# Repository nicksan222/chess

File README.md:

<div align="center">

# Chess

### A physical chessboard with software in its bones.

**64 magnetic sensors · 64 RGB lights · one Raspberry Pi · zero hidden magic**

[**Explore the hardware**](hardware/README.md) · [**Read the architecture**](docs/architecture.md) · [**Build from source**](docs/development.md) · [**Contribute**](.github/CONTRIBUTING.md)

<sub>Not a product mockup—the render above is generated from the <a href="hardware/cad/generated/board-assembly.blend">Blender assembly model in this repository</a>.</sub>

</div>

## About

Chess is an open-source smart chessboard designed to make the physical game
programmable. The design gives every square its own magnetic piece sensor and
clocked RGB light, ready to illuminate moves, threats, prompts, or entirely new
game modes. A Raspberry Pi Zero 2 W is intended to run the board directly in
Rust—there is no microcontroller, companion firmware, or private protocol in
the middle.

The interesting part is not only the board. Its mechanical dimensions,
electrical connectivity, firmware pin maps, KiCad project, Blender models, BOM,
and review images are generated from version-controlled contracts. Change a
measurement or signal once, regenerate, and let tests catch disagreement across
the stack.

| | |
|---|---|
| **Sense** | 64 DRV5032FC Hall sensors, eight compact polled TCA9554 banks |
| **Glow** | 64 individually addressable SK9822 RGB LEDs |
| **Think** | Raspberry Pi Zero 2 W targeting Rust on a Yocto Linux image |
| **Interact** | 12 labelled physical buttons and a 2.42-inch monochrome I²C OLED |
| **Build** | One 320 × 380 mm PCB, case, plate and twelve printable button caps |
| **Design** | Python contracts → KiCad 9 + Blender 4.5 + firmware mappings |

## Peek under the board

<table>
  <tr>
    <td width="58%">
      
    </td>
    <td width="42%">
      
    </td>
  </tr>
  <tr>
    <td align="center"><strong>Two printed parts. One PCB. No per-square wiring harness.</strong></td>
    <td align="center"><strong>Every square gets a sensor and an LED.</strong></td>
  </tr>
</table>

The visuals are review artifacts, not hand-drawn diagrams. Open the
[Blender assembly](hardware/cad/generated/board-assembly.blend), inspect the
[KiCad board](hardware/pcb/generated/chess-board.kicad_pcb), browse the
[generated schematic](hardware/pcb/generated/schematic/chess-board.svg), or
check every exact part in the [generated BOM](hardware/pcb/generated/bom.csv).

## Why this is fun to hack on

| Hardware you can reason about | Software with clean seams | A workflow built for changes |
|---|---|---|
| No second processor and no opaque wire protocol. The Pi talks to I²C expanders, SPI LEDs, GPIO buttons, and the display directly. | The chess engine, menu model, persistence, and Pi application live in separate Rust crates. | One devcontainer pins Rust, Ruff, KiCad, Blender, and Just. CI checks code, connectivity, layout, CAD, and the AArch64 firmware graph. |

```mermaid
flowchart LR
    P["Magnetic pieces"] --> H["64 × Hall sensors"]
    H --> E["8 × TCA9554 banks (2×4)"]
    E --> PI["Raspberry Pi Zero 2 W"]
    PI --> R["Rust chess + board logic"]
    PI --> L["64 × RGB LEDs"]
    PI --> UI["OLED + 12 buttons"]
```

Read the [architecture notes](docs/architecture.md) for the boundaries and the
[hardware design](docs/hardware.md) for the component choices behind them.

## Repository tour

| Path | What is inside |
|---|---|
| [`apps/firmware`](apps/firmware) | The Raspberry Pi process, system integration, and Yocto image |
| [`crates`](crates/README.md) | Chess rules, menu state, persistence, logging, and shared Rust code |
| [`hardware/shared`](hardware/shared) | The source of truth for dimensions, parts, wiring, and mappings |
| [`hardware/pcb`](hardware/pcb) | PCB definition, routing, validation, KiCad project, and BOM |
| [`hardware/cad`](hardware/cad) | Parametric enclosure generators, Blender models, and renders |
| [`docs`](docs/README.md) | Architecture, fabrication, power, assembly, and development guides |

## Start hacking

Clone the repository, open it in the included
[development container](.devcontainer/README.md), and then use its pinned
toolchain:

```bash
just --list       # discover everything the repo can do
just precommit    # fast code + hardware validation
just generate     # regenerate CAD and PCB review artifacts
just check        # run routine repository-wide validation
```

Physical-release and Linux-image validation remain explicit, separate gates:

```bash
just pcb-release
just firmware-check
```

Prefer a smaller loop? Every app, crate, and hardware domain owns its own
`justfile`:

```bash
just --justfile crates/chess/justfile check
just --justfile hardware/pcb/justfile review
just --justfile hardware/cad/justfile generate
```

See [`docs/development.md`](docs/development.md) for the full workflow.

Coding assistants start from [`AGENTS.md`](AGENTS.md). Claude Code, Codex and
other harnesses share one set of [skills and subagent roles](.agents/README.md),
including firmware, hardware, mechanical and manufacturing engineers; the
session you start delegates to them as needed.

## Project status

> [!IMPORTANT]
> **The current design is ready for review, not yet physically proven.** The
> mechanical design and `D-PROTOTYPE` PCB generate successfully, and automated
> DRC, connectivity, schematic parity and modeled electrical checks pass;
> meaningful ERC still requires declared electrical pin roles. No
> complete board has been built yet. Prototype one sensor/LED square before
> ordering the full PCB.

The chess model and supervised firmware process exist, and the firmware polls
buttons and Hall-sensor banks. The LED worker, provisioning workers, and final
physical validation are still open territory.
That makes this a particularly good time to challenge assumptions and shape the
project rather than only polish a finished product.

## Pick a quest

- **Firmware:** connect the Rust application to real Linux character devices.
- **Simulator:** make board behavior fast to test without a soldering iron.
- **Electronics:** review sensing, power, routing, and manufacturability.
- **Mechanical:** test clearances, print strategy, materials, and light diffusion.
- **Docs:** turn a pile of generated artifacts into a delightful build journey.

Start with [`CONTRIBUTING.md`](.github/CONTRIBUTING.md), bring large ideas to
[Discussions](https://github.com/nicksan222/chess/discussions), and use the issue
forms for focused bugs or features. First-time contributors are very welcome.

---

<div align="center">

**Build it. Break it. Teach it a new game.**

Released under the [MIT License](LICENSE) · Please follow the
[Code of Conduct](.github/CODE_OF_CONDUCT.md) · Report security issues via
[`SECURITY.md`](.github/SECURITY.md)

</div>

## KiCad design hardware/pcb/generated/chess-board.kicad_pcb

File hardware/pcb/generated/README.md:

# Generated PCB

Source: `pcb.board.board.Board()`. Regenerate with `PYTHONPATH=hardware python3 -m pcb.board.generate`.

Open `chess-board.kicad_pro` in KiCad. Schematics embed all symbols and show the declared pin maps; PCB footprints come from component land patterns. The exported schematic netlist is checked against every declared connected pin.

The PCB includes routed copper, filled internal rail planes, mounting holes and assembly markings. `chess-board.glb` is the native 3D assembly imported by CAD; `models/` contains portable STEP bodies and `3d-models.json` records fidelity and provenance. ERC/DRC findings are in `erc.json` and `drc.json`. Electrical pin roles are unspecified; ERC does not validate driver/power compatibility. `board-top.svg` and `board-top.png` show the same copper view; bottom views are mirrored. `board-connections.svg` shows logical connectivity as dashed airwires, not extra copper. `manifest.json` lists remaining work. The fabrication ZIP contains Gerbers and drill files; generating it does not approve manufacturing.

Board-specific sensing and button simulations passed; results are in `electrical-checks/`. These use ideal sensor, contact and external GPIO bias models; I2C, magnetic margins, firmware debounce and a complete board model remain untested.

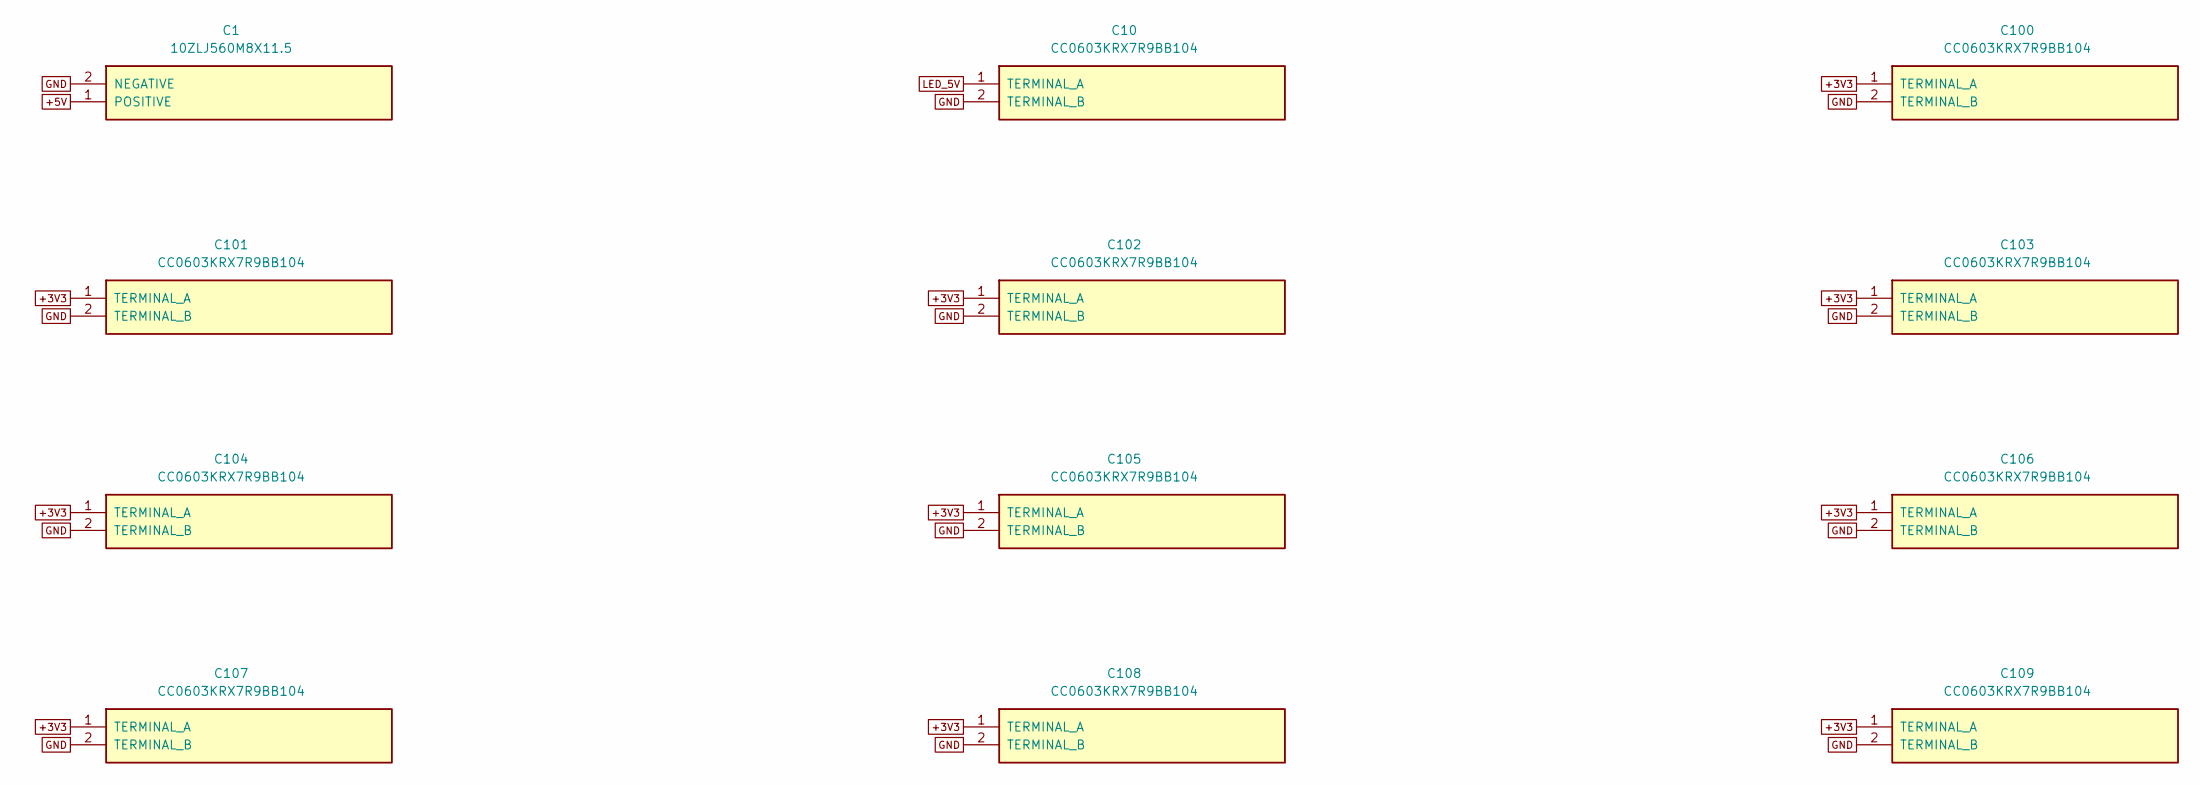
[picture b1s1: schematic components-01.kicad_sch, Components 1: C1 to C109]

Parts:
C1: 10ZLJ560M8X11.5; CAP_560U
C10, C100, C101, C102, C103, C104, C105, C106, C107, C108, C109: CC0603KRX7R9BB104; CAP_100N

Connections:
+3V3: C100.1 (TERMINAL_A), C101.1 (TERMINAL_A), C102.1 (TERMINAL_A), C103.1 (TERMINAL_A), C104.1 (TERMINAL_A), C105.1 (TERMINAL_A), C106.1 (TERMINAL_A), C107.1 (TERMINAL_A), C108.1 (TERMINAL_A), C109.1 (TERMINAL_A); also elsewhere on the board
+5V: C1.1 (POSITIVE); also elsewhere on the board
GND: C1.2 (NEGATIVE), C10.2 (TERMINAL_B), C100.2 (TERMINAL_B), C101.2 (TERMINAL_B), C102.2 (TERMINAL_B), C103.2 (TERMINAL_B), C104.2 (TERMINAL_B), C105.2 (TERMINAL_B), C106.2 (TERMINAL_B), C107.2 (TERMINAL_B), C108.2 (TERMINAL_B), C109.2 (TERMINAL_B); also elsewhere on the board
LED_5V: C10.1 (TERMINAL_A); also elsewhere on the board

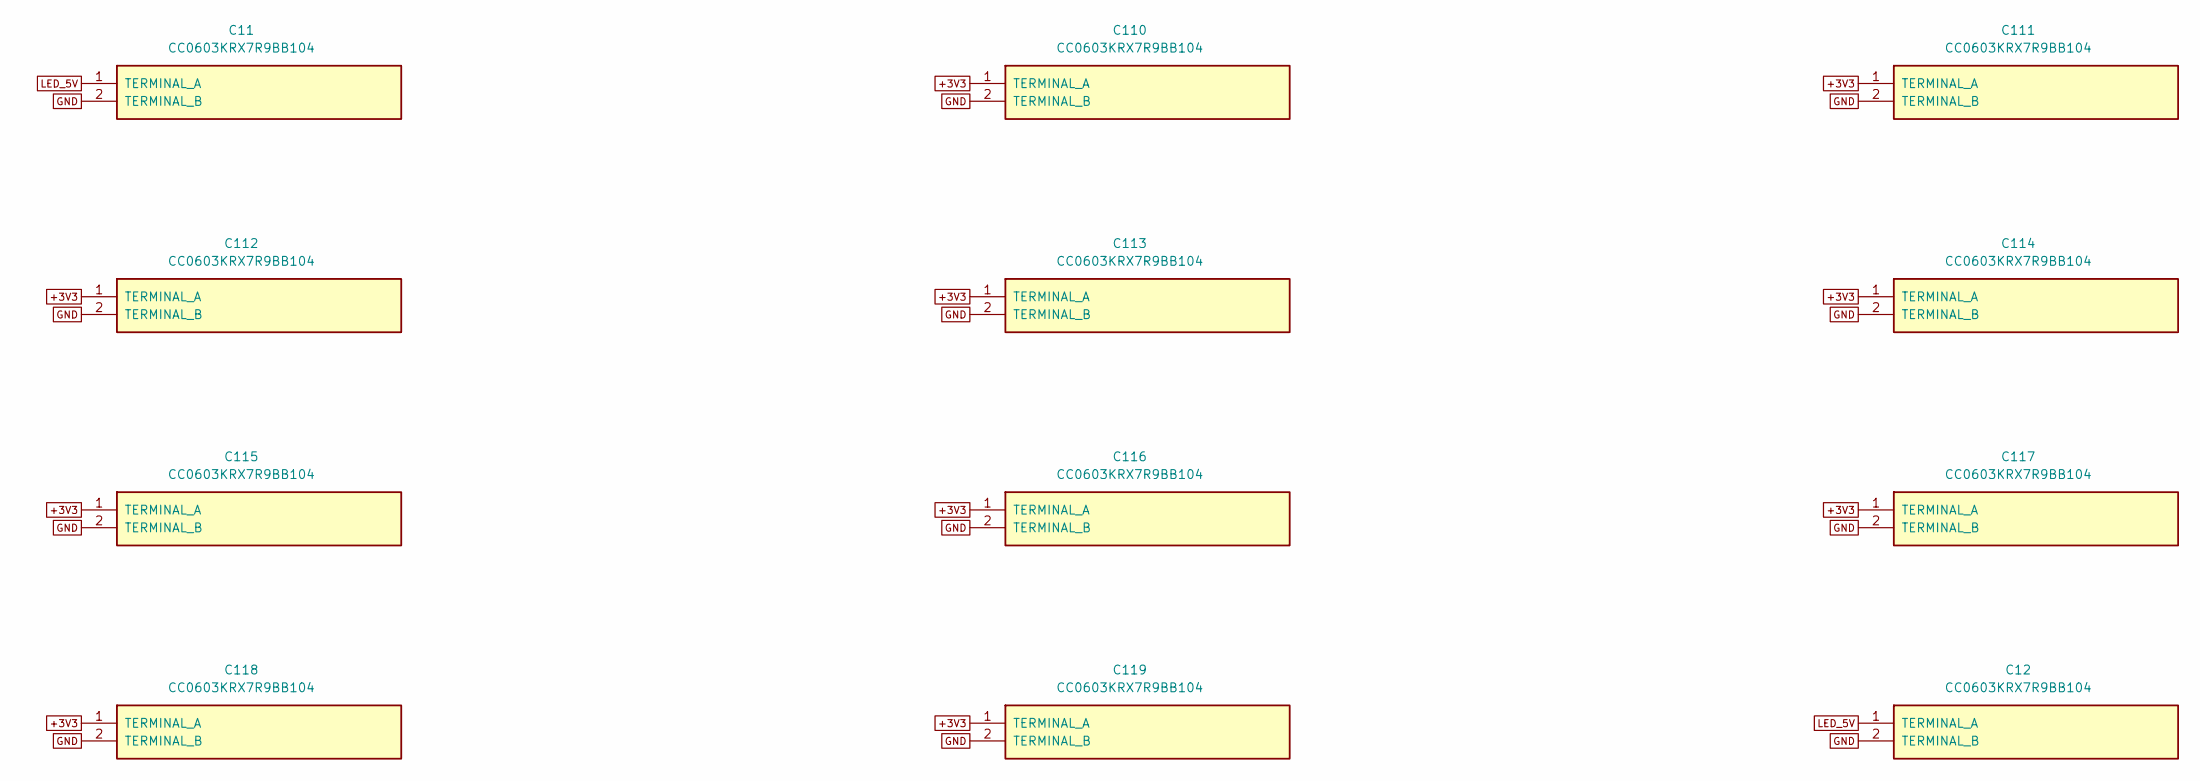
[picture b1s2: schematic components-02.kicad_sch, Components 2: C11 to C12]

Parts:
C11, C12, C110, C111, C112, C113, C114, C115, C116, C117, C118, C119: CC0603KRX7R9BB104; CAP_100N

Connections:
+3V3: C110.1 (TERMINAL_A), C111.1 (TERMINAL_A), C112.1 (TERMINAL_A), C113.1 (TERMINAL_A), C114.1 (TERMINAL_A), C115.1 (TERMINAL_A), C116.1 (TERMINAL_A), C117.1 (TERMINAL_A), C118.1 (TERMINAL_A), C119.1 (TERMINAL_A); also elsewhere on the board
GND: C11.2 (TERMINAL_B), C12.2 (TERMINAL_B), C110.2 (TERMINAL_B), C111.2 (TERMINAL_B), C112.2 (TERMINAL_B), C113.2 (TERMINAL_B), C114.2 (TERMINAL_B), C115.2 (TERMINAL_B), C116.2 (TERMINAL_B), C117.2 (TERMINAL_B), C118.2 (TERMINAL_B), C119.2 (TERMINAL_B); also elsewhere on the board
LED_5V: C11.1 (TERMINAL_A), C12.1 (TERMINAL_A); also elsewhere on the board

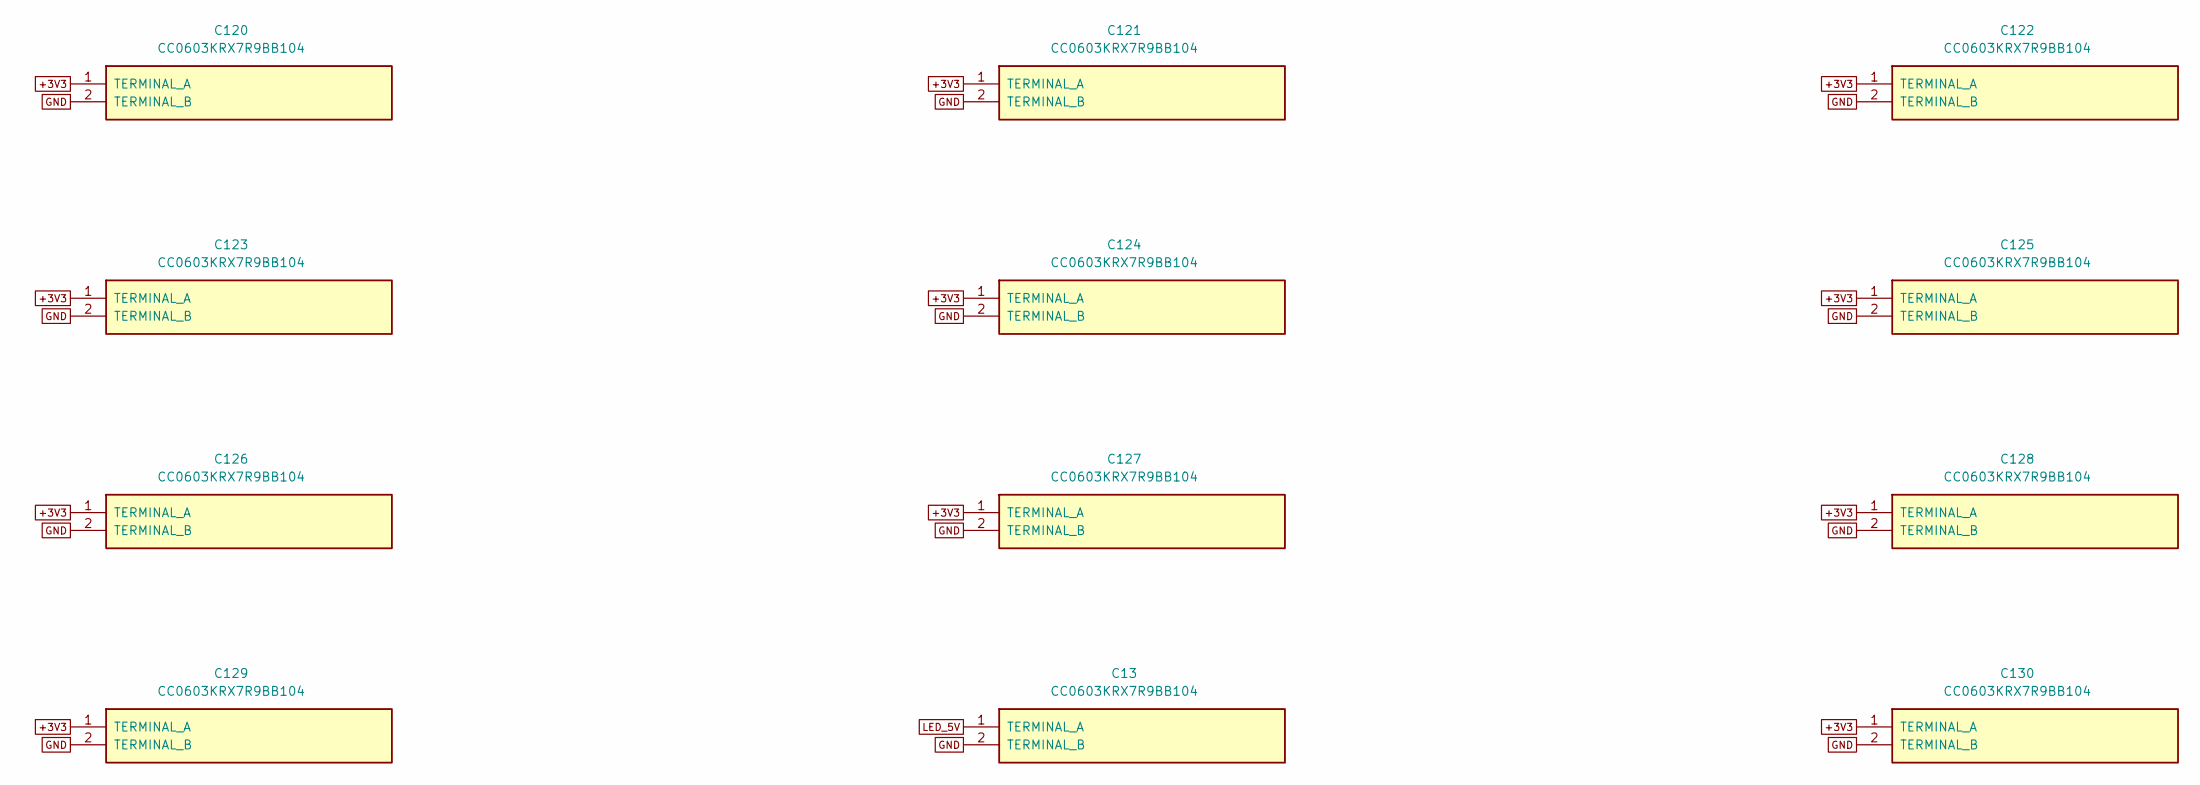
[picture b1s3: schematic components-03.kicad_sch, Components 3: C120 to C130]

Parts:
C13, C120, C121, C122, C123, C124, C125, C126, C127, C128, C129, C130: CC0603KRX7R9BB104; CAP_100N

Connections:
+3V3: C120.1 (TERMINAL_A), C121.1 (TERMINAL_A), C122.1 (TERMINAL_A), C123.1 (TERMINAL_A), C124.1 (TERMINAL_A), C125.1 (TERMINAL_A), C126.1 (TERMINAL_A), C127.1 (TERMINAL_A), C128.1 (TERMINAL_A), C129.1 (TERMINAL_A), C130.1 (TERMINAL_A); also elsewhere on the board
GND: C13.2 (TERMINAL_B), C120.2 (TERMINAL_B), C121.2 (TERMINAL_B), C122.2 (TERMINAL_B), C123.2 (TERMINAL_B), C124.2 (TERMINAL_B), C125.2 (TERMINAL_B), C126.2 (TERMINAL_B), C127.2 (TERMINAL_B), C128.2 (TERMINAL_B), C129.2 (TERMINAL_B), C130.2 (TERMINAL_B); also elsewhere on the board
LED_5V: C13.1 (TERMINAL_A); also elsewhere on the board

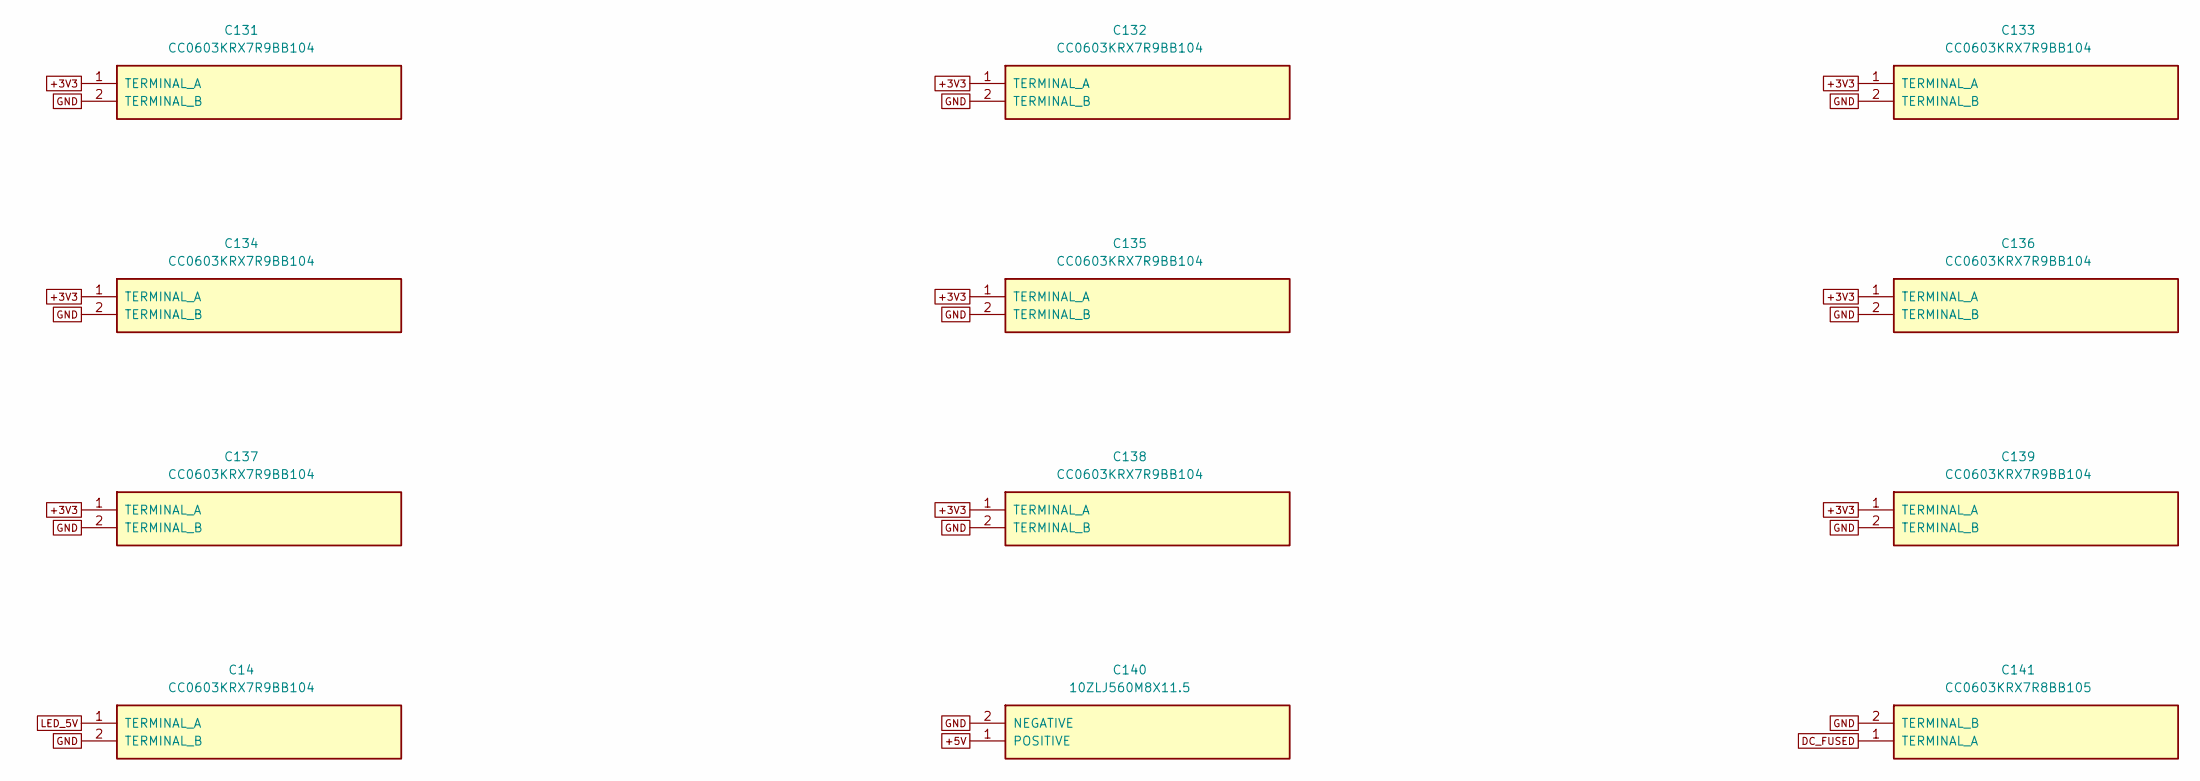
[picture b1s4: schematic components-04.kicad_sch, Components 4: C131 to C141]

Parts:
C14, C131, C132, C133, C134, C135, C136, C137, C138, C139: CC0603KRX7R9BB104; CAP_100N
C140: 10ZLJ560M8X11.5; CAP_560U
C141: CC0603KRX7R8BB105; CAP_1U

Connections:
+3V3: C131.1 (TERMINAL_A), C132.1 (TERMINAL_A), C133.1 (TERMINAL_A), C134.1 (TERMINAL_A), C135.1 (TERMINAL_A), C136.1 (TERMINAL_A), C137.1 (TERMINAL_A), C138.1 (TERMINAL_A), C139.1 (TERMINAL_A); also elsewhere on the board
+5V: C140.1 (POSITIVE); also elsewhere on the board
DC_FUSED: C141.1 (TERMINAL_A); also elsewhere on the board
GND: C14.2 (TERMINAL_B), C131.2 (TERMINAL_B), C132.2 (TERMINAL_B), C133.2 (TERMINAL_B), C134.2 (TERMINAL_B), C135.2 (TERMINAL_B), C136.2 (TERMINAL_B), C137.2 (TERMINAL_B), C138.2 (TERMINAL_B), C139.2 (TERMINAL_B), C140.2 (NEGATIVE), C141.2 (TERMINAL_B); also elsewhere on the board
LED_5V: C14.1 (TERMINAL_A); also elsewhere on the board

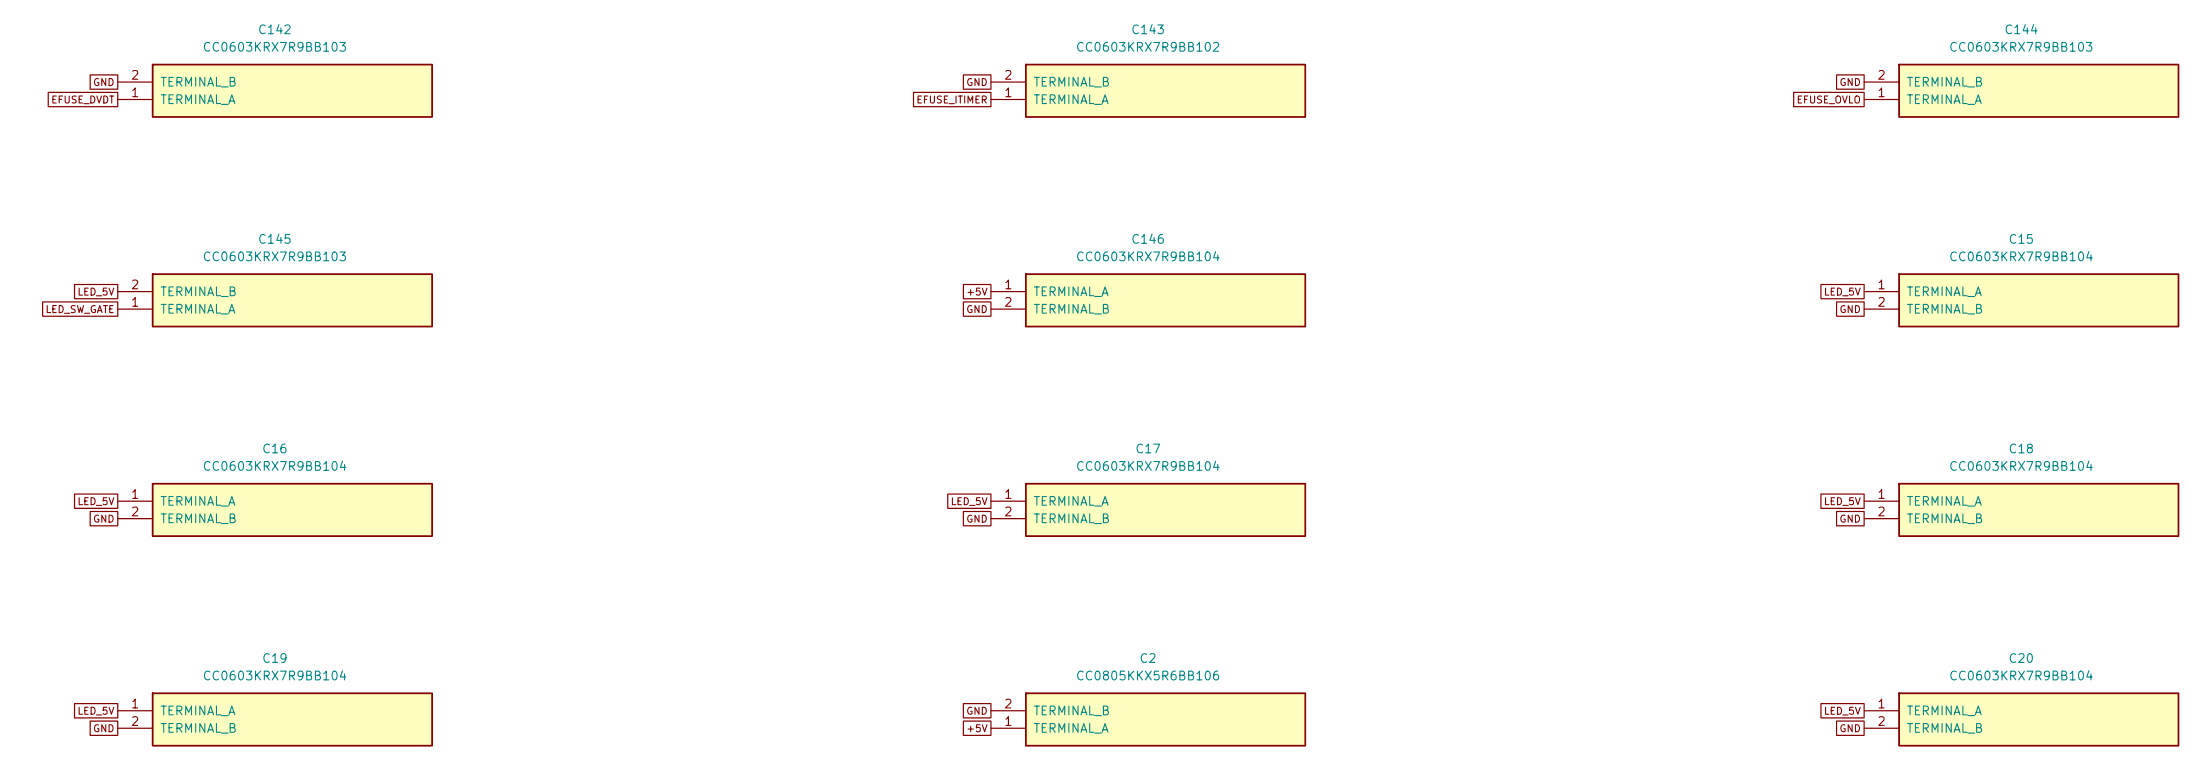
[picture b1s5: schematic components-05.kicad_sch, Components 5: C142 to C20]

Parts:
C2: CC0805KKX5R6BB106; CAP_10U
C15, C16, C17, C18, C19, C20, C146: CC0603KRX7R9BB104; CAP_100N
C142, C144, C145: CC0603KRX7R9BB103; CAP_10N
C143: CC0603KRX7R9BB102; CAP_1N

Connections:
+5V: C2.1 (TERMINAL_A), C146.1 (TERMINAL_A); also elsewhere on the board
EFUSE_DVDT: C142.1 (TERMINAL_A); also elsewhere on the board
EFUSE_ITIMER: C143.1 (TERMINAL_A); also elsewhere on the board
EFUSE_OVLO: C144.1 (TERMINAL_A); also elsewhere on the board
GND: C2.2 (TERMINAL_B), C15.2 (TERMINAL_B), C16.2 (TERMINAL_B), C17.2 (TERMINAL_B), C18.2 (TERMINAL_B), C19.2 (TERMINAL_B), C20.2 (TERMINAL_B), C142.2 (TERMINAL_B), C143.2 (TERMINAL_B), C144.2 (TERMINAL_B), C146.2 (TERMINAL_B); also elsewhere on the board
LED_5V: C15.1 (TERMINAL_A), C16.1 (TERMINAL_A), C17.1 (TERMINAL_A), C18.1 (TERMINAL_A), C19.1 (TERMINAL_A), C20.1 (TERMINAL_A), C145.2 (TERMINAL_B); also elsewhere on the board
LED_SW_GATE: C145.1 (TERMINAL_A); also elsewhere on the board

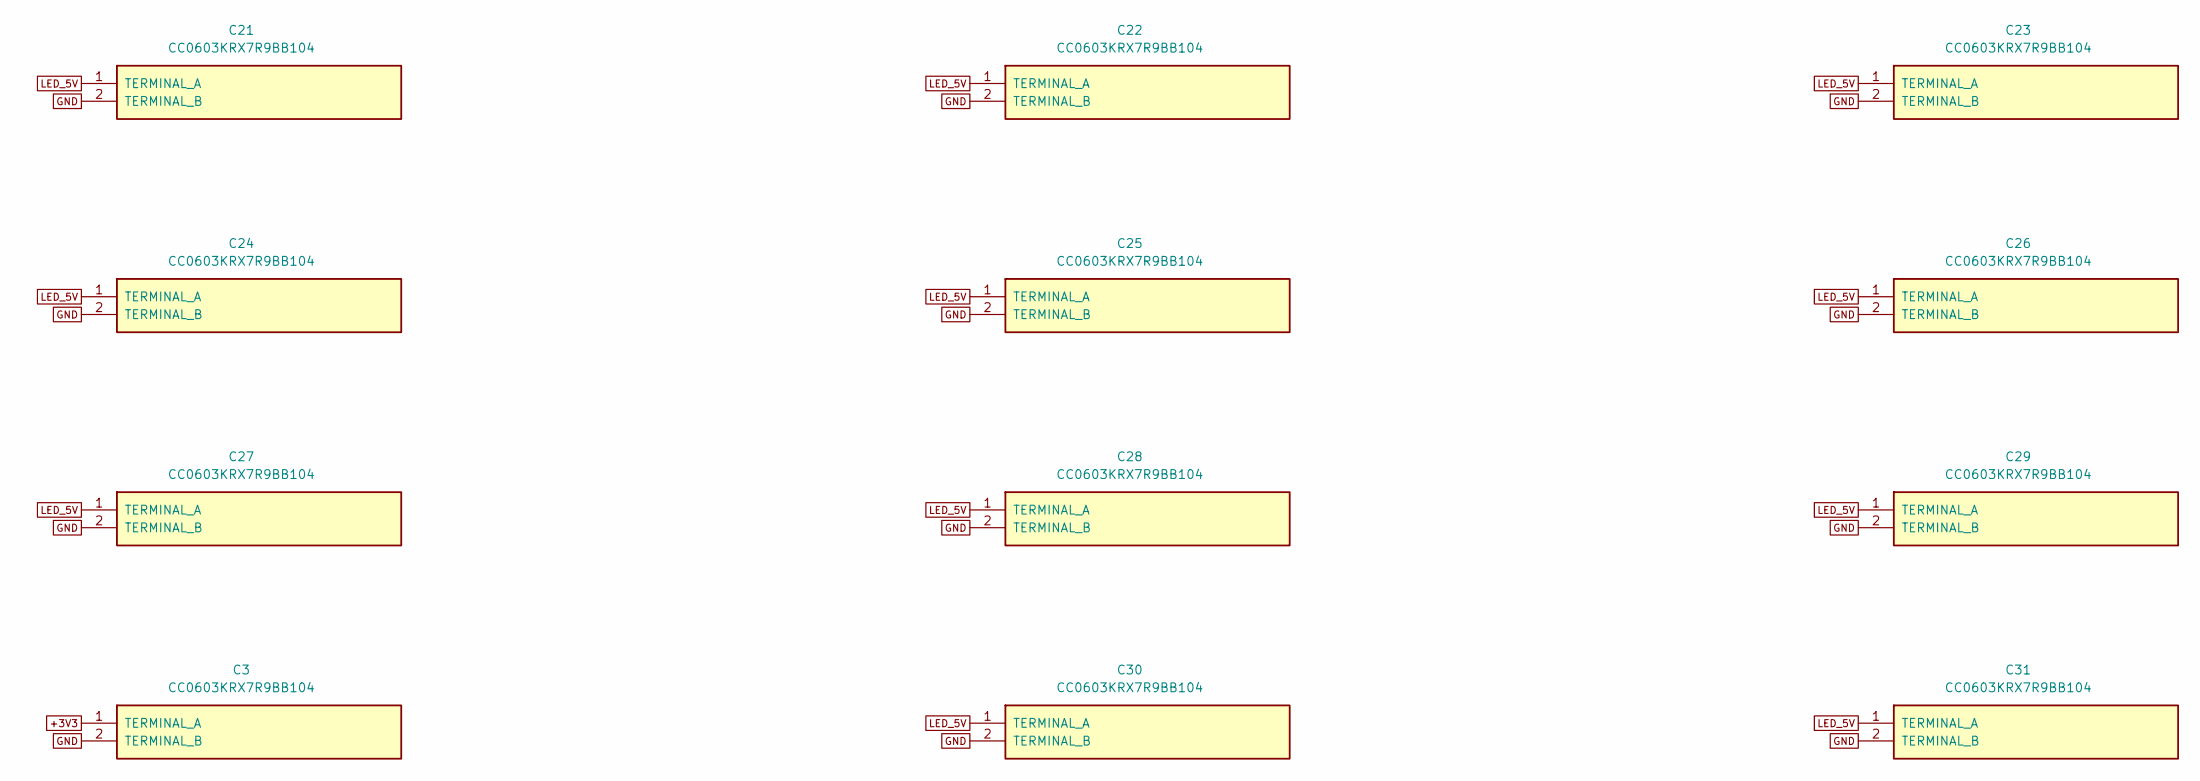
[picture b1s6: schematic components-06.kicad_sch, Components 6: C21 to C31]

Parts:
C3, C21, C22, C23, C24, C25, C26, C27, C28, C29, C30, C31: CC0603KRX7R9BB104; CAP_100N

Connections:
+3V3: C3.1 (TERMINAL_A); also elsewhere on the board
GND: C3.2 (TERMINAL_B), C21.2 (TERMINAL_B), C22.2 (TERMINAL_B), C23.2 (TERMINAL_B), C24.2 (TERMINAL_B), C25.2 (TERMINAL_B), C26.2 (TERMINAL_B), C27.2 (TERMINAL_B), C28.2 (TERMINAL_B), C29.2 (TERMINAL_B), C30.2 (TERMINAL_B), C31.2 (TERMINAL_B); also elsewhere on the board
LED_5V: C21.1 (TERMINAL_A), C22.1 (TERMINAL_A), C23.1 (TERMINAL_A), C24.1 (TERMINAL_A), C25.1 (TERMINAL_A), C26.1 (TERMINAL_A), C27.1 (TERMINAL_A), C28.1 (TERMINAL_A), C29.1 (TERMINAL_A), C30.1 (TERMINAL_A), C31.1 (TERMINAL_A); also elsewhere on the board

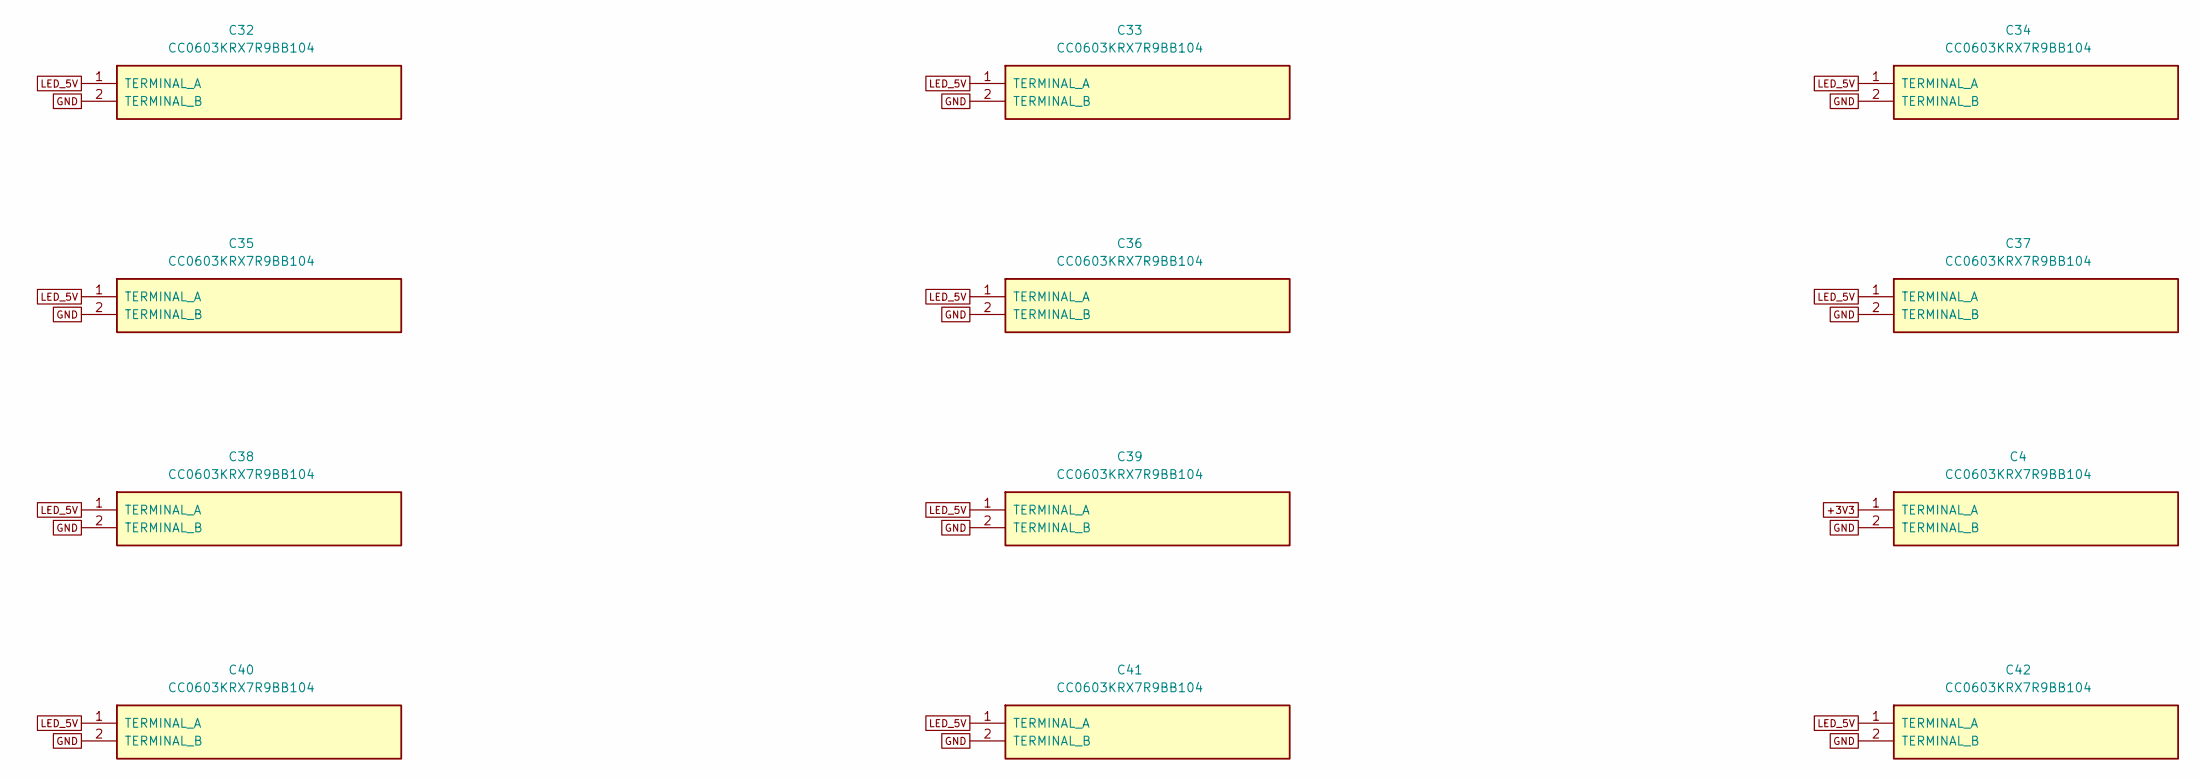
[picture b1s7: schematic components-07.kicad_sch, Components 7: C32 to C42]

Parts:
C4, C32, C33, C34, C35, C36, C37, C38, C39, C40, C41, C42: CC0603KRX7R9BB104; CAP_100N

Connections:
+3V3: C4.1 (TERMINAL_A); also elsewhere on the board
GND: C4.2 (TERMINAL_B), C32.2 (TERMINAL_B), C33.2 (TERMINAL_B), C34.2 (TERMINAL_B), C35.2 (TERMINAL_B), C36.2 (TERMINAL_B), C37.2 (TERMINAL_B), C38.2 (TERMINAL_B), C39.2 (TERMINAL_B), C40.2 (TERMINAL_B), C41.2 (TERMINAL_B), C42.2 (TERMINAL_B); also elsewhere on the board
LED_5V: C32.1 (TERMINAL_A), C33.1 (TERMINAL_A), C34.1 (TERMINAL_A), C35.1 (TERMINAL_A), C36.1 (TERMINAL_A), C37.1 (TERMINAL_A), C38.1 (TERMINAL_A), C39.1 (TERMINAL_A), C40.1 (TERMINAL_A), C41.1 (TERMINAL_A), C42.1 (TERMINAL_A); also elsewhere on the board

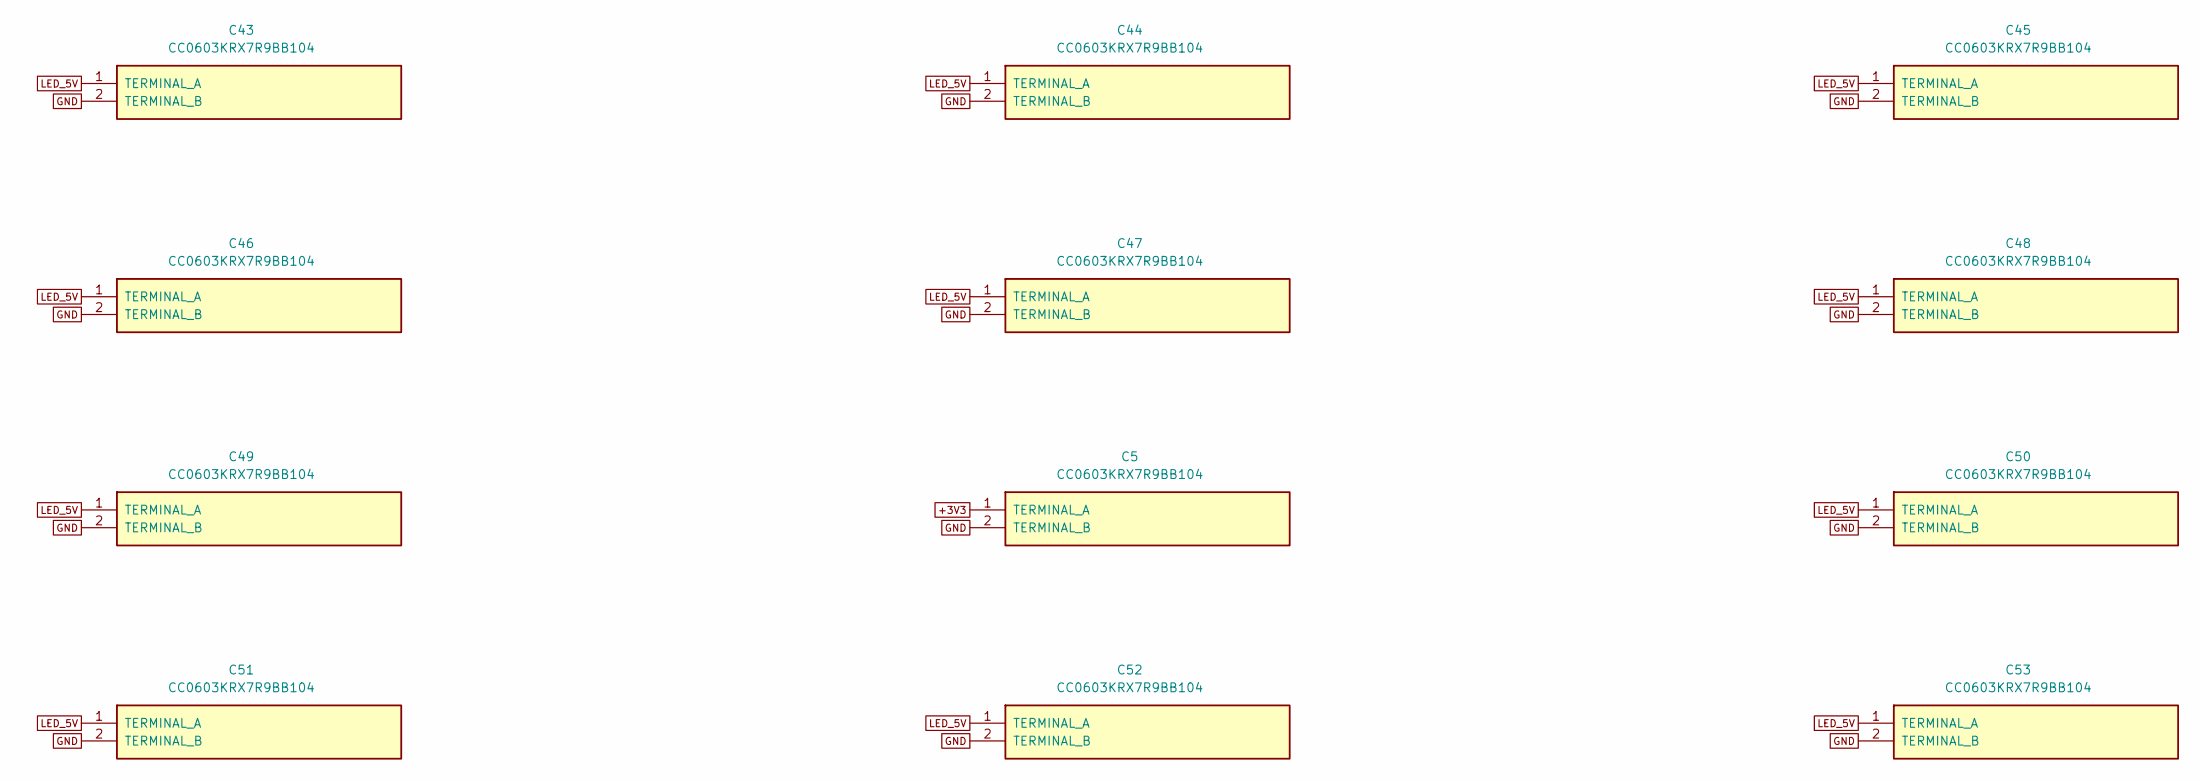
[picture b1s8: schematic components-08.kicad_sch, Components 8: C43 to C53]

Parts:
C5, C43, C44, C45, C46, C47, C48, C49, C50, C51, C52, C53: CC0603KRX7R9BB104; CAP_100N

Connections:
+3V3: C5.1 (TERMINAL_A); also elsewhere on the board
GND: C5.2 (TERMINAL_B), C43.2 (TERMINAL_B), C44.2 (TERMINAL_B), C45.2 (TERMINAL_B), C46.2 (TERMINAL_B), C47.2 (TERMINAL_B), C48.2 (TERMINAL_B), C49.2 (TERMINAL_B), C50.2 (TERMINAL_B), C51.2 (TERMINAL_B), C52.2 (TERMINAL_B), C53.2 (TERMINAL_B); also elsewhere on the board
LED_5V: C43.1 (TERMINAL_A), C44.1 (TERMINAL_A), C45.1 (TERMINAL_A), C46.1 (TERMINAL_A), C47.1 (TERMINAL_A), C48.1 (TERMINAL_A), C49.1 (TERMINAL_A), C50.1 (TERMINAL_A), C51.1 (TERMINAL_A), C52.1 (TERMINAL_A), C53.1 (TERMINAL_A); also elsewhere on the board

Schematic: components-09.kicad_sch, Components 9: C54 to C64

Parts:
C6, C54, C55, C56, C57, C58, C59, C60, C61, C62, C63, C64: CC0603KRX7R9BB104; CAP_100N

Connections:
+3V3: C6.1 (TERMINAL_A); also elsewhere on the board
GND: C6.2 (TERMINAL_B), C54.2 (TERMINAL_B), C55.2 (TERMINAL_B), C56.2 (TERMINAL_B), C57.2 (TERMINAL_B), C58.2 (TERMINAL_B), C59.2 (TERMINAL_B), C60.2 (TERMINAL_B), C61.2 (TERMINAL_B), C62.2 (TERMINAL_B), C63.2 (TERMINAL_B), C64.2 (TERMINAL_B); also elsewhere on the board
LED_5V: C54.1 (TERMINAL_A), C55.1 (TERMINAL_A), C56.1 (TERMINAL_A), C57.1 (TERMINAL_A), C58.1 (TERMINAL_A), C59.1 (TERMINAL_A), C60.1 (TERMINAL_A), C61.1 (TERMINAL_A), C62.1 (TERMINAL_A), C63.1 (TERMINAL_A), C64.1 (TERMINAL_A); also elsewhere on the board

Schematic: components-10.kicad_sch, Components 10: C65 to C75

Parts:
C7, C65, C66, C67, C68, C69, C70, C71, C72, C73, C74, C75: CC0603KRX7R9BB104; CAP_100N

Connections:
+3V3: C72.1 (TERMINAL_A), C73.1 (TERMINAL_A), C74.1 (TERMINAL_A), C75.1 (TERMINAL_A); also elsewhere on the board
+5V: C7.1 (TERMINAL_A); also elsewhere on the board
GND: C7.2 (TERMINAL_B), C65.2 (TERMINAL_B), C66.2 (TERMINAL_B), C67.2 (TERMINAL_B), C68.2 (TERMINAL_B), C69.2 (TERMINAL_B), C70.2 (TERMINAL_B), C71.2 (TERMINAL_B), C72.2 (TERMINAL_B), C73.2 (TERMINAL_B), C74.2 (TERMINAL_B), C75.2 (TERMINAL_B); also elsewhere on the board
LED_5V: C65.1 (TERMINAL_A), C66.1 (TERMINAL_A), C67.1 (TERMINAL_A), C68.1 (TERMINAL_A), C69.1 (TERMINAL_A), C70.1 (TERMINAL_A), C71.1 (TERMINAL_A); also elsewhere on the board

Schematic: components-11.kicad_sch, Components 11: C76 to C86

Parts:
C8, C76, C77, C78, C79, C80, C81, C82, C83, C84, C85, C86: CC0603KRX7R9BB104; CAP_100N

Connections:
+3V3: C76.1 (TERMINAL_A), C77.1 (TERMINAL_A), C78.1 (TERMINAL_A), C79.1 (TERMINAL_A), C80.1 (TERMINAL_A), C81.1 (TERMINAL_A), C82.1 (TERMINAL_A), C83.1 (TERMINAL_A), C84.1 (TERMINAL_A), C85.1 (TERMINAL_A), C86.1 (TERMINAL_A); also elsewhere on the board
GND: C8.2 (TERMINAL_B), C76.2 (TERMINAL_B), C77.2 (TERMINAL_B), C78.2 (TERMINAL_B), C79.2 (TERMINAL_B), C80.2 (TERMINAL_B), C81.2 (TERMINAL_B), C82.2 (TERMINAL_B), C83.2 (TERMINAL_B), C84.2 (TERMINAL_B), C85.2 (TERMINAL_B), C86.2 (TERMINAL_B); also elsewhere on the board
LED_5V: C8.1 (TERMINAL_A); also elsewhere on the board

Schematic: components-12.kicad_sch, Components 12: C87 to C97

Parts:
C9, C87, C88, C89, C90, C91, C92, C93, C94, C95, C96, C97: CC0603KRX7R9BB104; CAP_100N

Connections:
+3V3: C87.1 (TERMINAL_A), C88.1 (TERMINAL_A), C89.1 (TERMINAL_A), C90.1 (TERMINAL_A), C91.1 (TERMINAL_A), C92.1 (TERMINAL_A), C93.1 (TERMINAL_A), C94.1 (TERMINAL_A), C95.1 (TERMINAL_A), C96.1 (TERMINAL_A), C97.1 (TERMINAL_A); also elsewhere on the board
GND: C9.2 (TERMINAL_B), C87.2 (TERMINAL_B), C88.2 (TERMINAL_B), C89.2 (TERMINAL_B), C90.2 (TERMINAL_B), C91.2 (TERMINAL_B), C92.2 (TERMINAL_B), C93.2 (TERMINAL_B), C94.2 (TERMINAL_B), C95.2 (TERMINAL_B), C96.2 (TERMINAL_B), C97.2 (TERMINAL_B); also elsewhere on the board
LED_5V: C9.1 (TERMINAL_A); also elsewhere on the board

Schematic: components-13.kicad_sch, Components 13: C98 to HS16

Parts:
C98, C99: CC0603KRX7R9BB104; CAP_100N
D1: SMBJ12CA; TVS_12V0
F1: 0453002.MR; FUSE_2A
HS1, HS10, HS11, HS12, HS13, HS14, HS15, HS16: DRV5032FCDBZR; HALL_SENSOR

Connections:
+3V3: C98.1 (TERMINAL_A), C99.1 (TERMINAL_A), HS1.1 (SUPPLY), HS10.1 (SUPPLY), HS11.1 (SUPPLY), HS12.1 (SUPPLY), HS13.1 (SUPPLY), HS14.1 (SUPPLY), HS15.1 (SUPPLY), HS16.1 (SUPPLY); also elsewhere on the board
DC_FUSED: D1.1 (PROTECTED_INPUT), F1.2 (FUSED_OUTPUT); also elsewhere on the board
DC_IN: F1.1 (UNFUSED_INPUT); also elsewhere on the board
GND: C98.2 (TERMINAL_B), C99.2 (TERMINAL_B), D1.2 (GROUND), HS1.3 (GROUND), HS10.3 (GROUND), HS11.3 (GROUND), HS12.3 (GROUND), HS13.3 (GROUND), HS14.3 (GROUND), HS15.3 (GROUND), HS16.3 (GROUND); also elsewhere on the board
SQ_A1: HS1.2 (ACTIVE_LOW_OUTPUT); also elsewhere on the board
SQ_A4: HS13.2 (ACTIVE_LOW_OUTPUT); also elsewhere on the board
SQ_B3: HS10.2 (ACTIVE_LOW_OUTPUT); also elsewhere on the board
SQ_B4: HS14.2 (ACTIVE_LOW_OUTPUT); also elsewhere on the board
SQ_C3: HS11.2 (ACTIVE_LOW_OUTPUT); also elsewhere on the board
SQ_C4: HS15.2 (ACTIVE_LOW_OUTPUT); also elsewhere on the board
SQ_D3: HS12.2 (ACTIVE_LOW_OUTPUT); also elsewhere on the board
SQ_D4: HS16.2 (ACTIVE_LOW_OUTPUT); also elsewhere on the board

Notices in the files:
README.md:
License: MIT
